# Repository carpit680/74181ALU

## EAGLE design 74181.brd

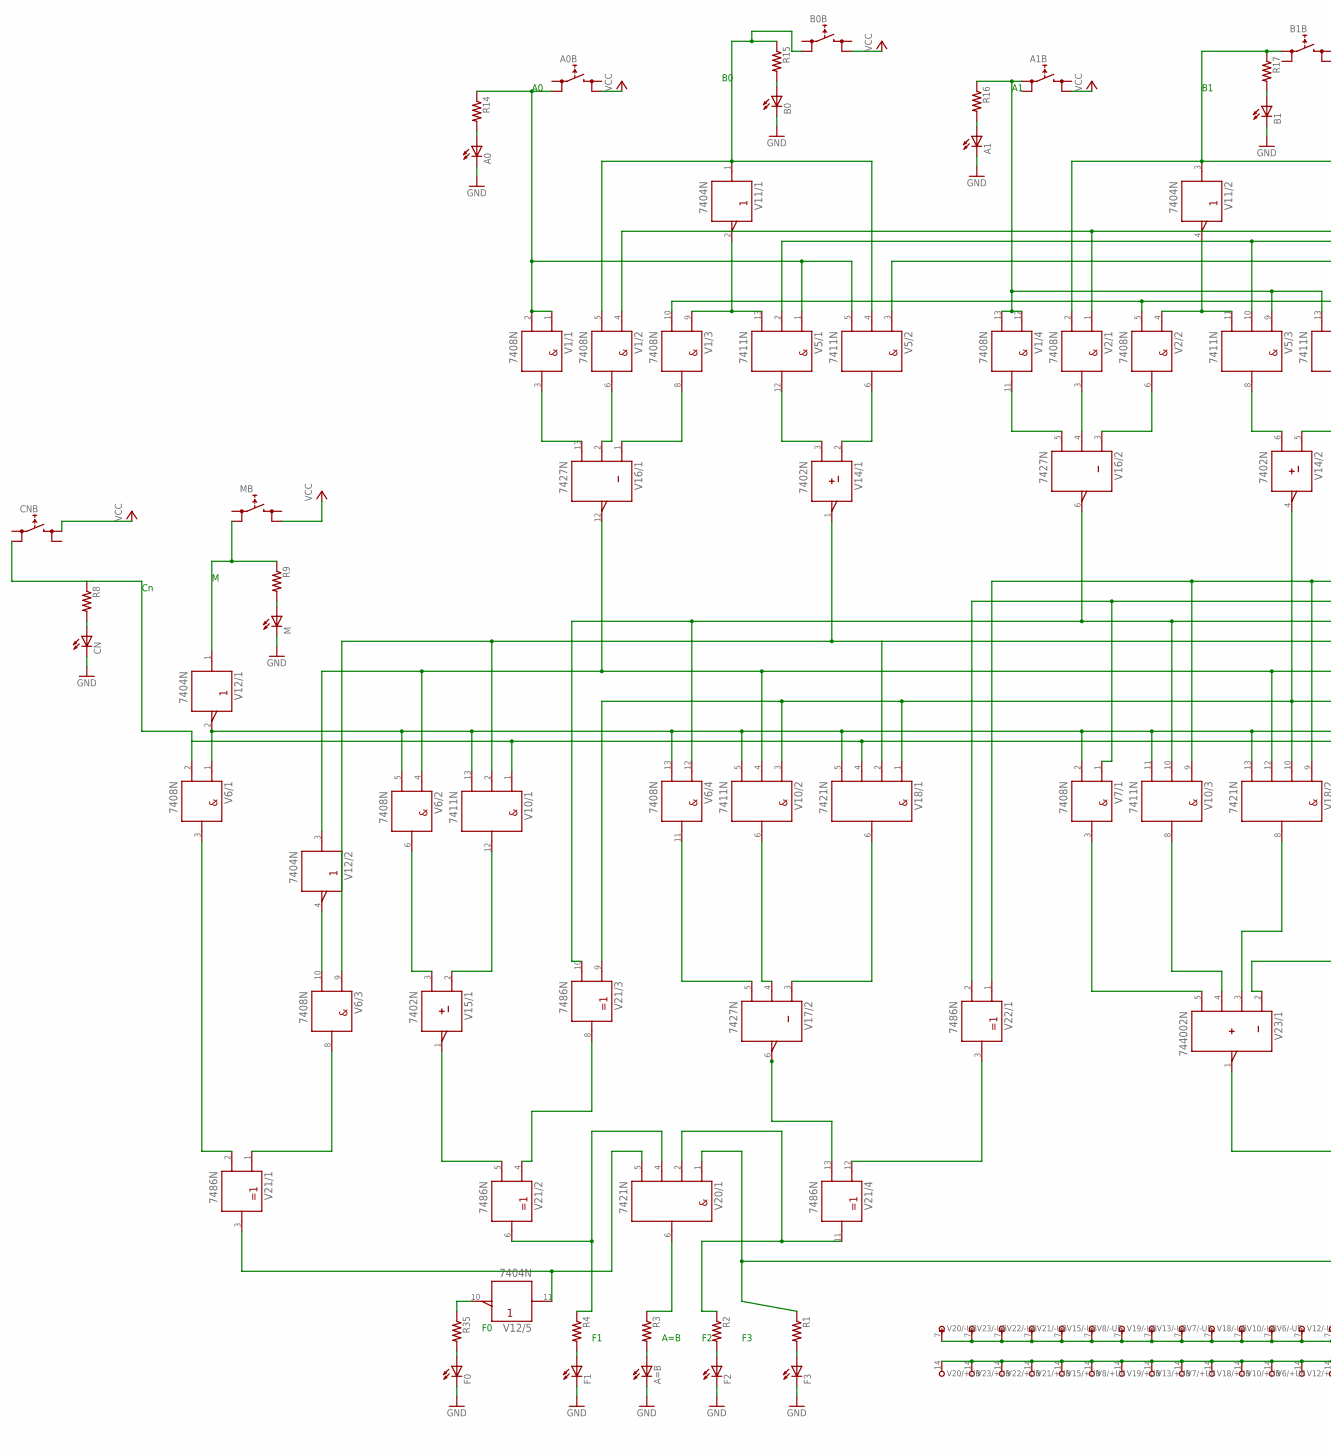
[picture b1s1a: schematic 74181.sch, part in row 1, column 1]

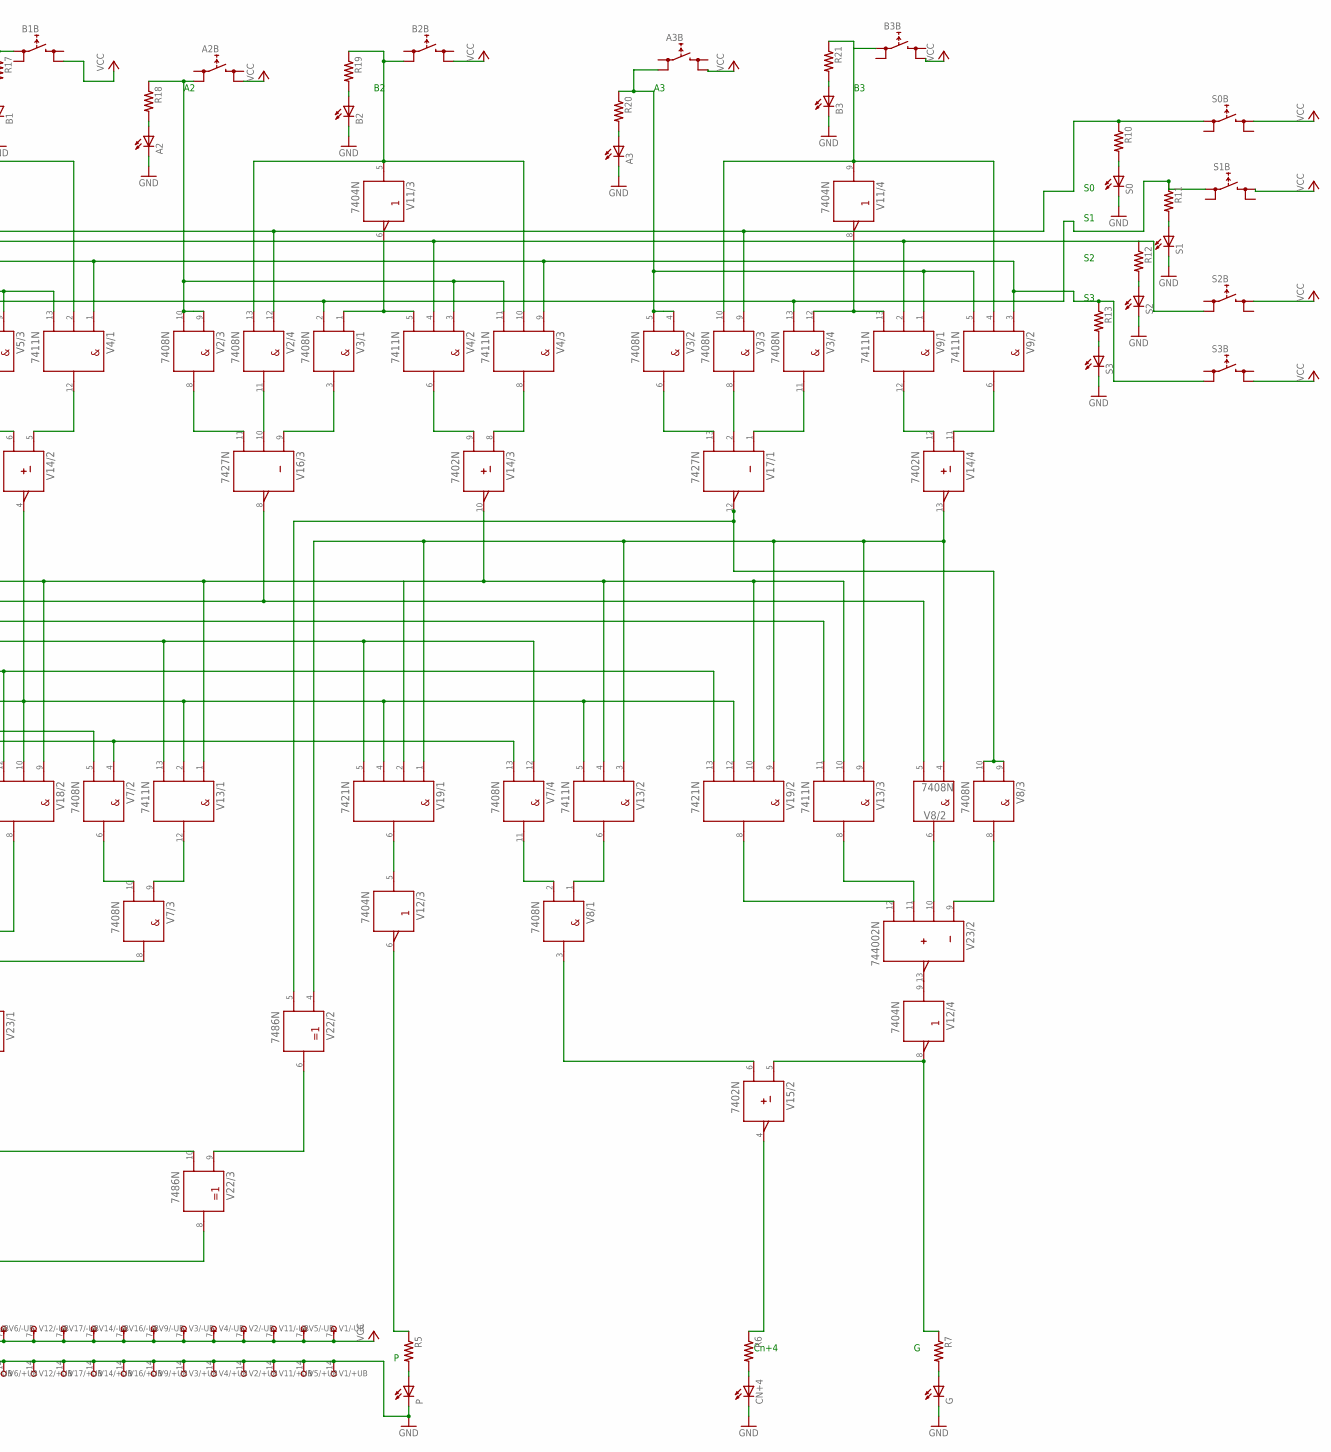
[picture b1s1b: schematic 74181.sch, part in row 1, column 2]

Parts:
A0, A1, A2, A3: LEDCHIP-LED0603; CHIP-LED0603
A0B, A1B, A2B, A3B: REKN
A=B: LEDCHIP-LED0603; CHIP-LED0603
B0, B1, B2, B3: LEDCHIP-LED0603; CHIP-LED0603
B0B, B1B, B2B, B3B: REKN
CN: LEDCHIP-LED0603; CHIP-LED0603
CN+4: LEDCHIP-LED0603; CHIP-LED0603
CNB: REKN
F0, F1, F2, F3: LEDCHIP-LED0603; CHIP-LED0603
G: LEDCHIP-LED0603; CHIP-LED0603
M: LEDCHIP-LED0603; CHIP-LED0603
MB: REKN
P: LEDCHIP-LED0603; CHIP-LED0603
R1, R2, R3, R4, R5, R6, R7, R8, R9, R10, R11, R12, R13, R14, R15, R16, R17, R18, R19, R20, R21, R35: R-US_R0603; R0603
S0, S1, S2, S3: LEDCHIP-LED0603; CHIP-LED0603
S0B, S1B, S2B, S3B: REKN
V1, V2, V3, V6, V7, V8: 7408N; DIL14
V4, V5, V9, V10, V13: 7411N; DIL14
V11, V12: 7404N; DIL14
V14, V15: 7402N; DIL14
V16, V17: 7427N; DIL14
V18, V19, V20: 7421N; DIL14
V21, V22: 7486N; DIL14
V23: 744002N; DIL14

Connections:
!F!0: V12.11 (A), V20.5 (D), V21.3 (Y)
GND: A0.C, A1.C, A2.C, A3.C, A=B.C, B0.C, B1.C, B2.C, B3.C, CN.C, CN+4.C, F0.C, F1.C, F2.C, F3.C, G.C, M.C, P.C, S0.C, S1.C, S2.C, S3.C, V1.14 (+UB), V2.14 (+UB), V3.14 (+UB), V4.14 (+UB), V5.14 (+UB), V6.14 (+UB), V7.14 (+UB), V8.14 (+UB), V9.14 (+UB), V10.14 (+UB), V11.14 (+UB), V12.14 (+UB), V13.14 (+UB), V14.14 (+UB), V15.14 (+UB), V16.14 (+UB), V17.14 (+UB), V18.14 (+UB), V19.14 (+UB), V20.14 (+UB), V21.14 (+UB), V22.14 (+UB), V23.14 (+UB)
unnamed: V1.9 (A), V5.13 (C), V11.2 (Y)
unnamed: V2.4 (A), V5.11 (C), V11.4 (Y)
unnamed: V3.1 (A), V4.5 (C), V11.6 (Y)
unnamed: V3.12 (A), V9.13 (C), V11.8 (Y)
unnamed: V1.3 (Y), V16.13 (C)
unnamed: V1.6 (Y), V16.2 (B)
unnamed: V1.8 (Y), V16.1 (A)
unnamed: V5.12 (Y), V14.3 (B)
unnamed: V5.6 (Y), V14.2 (A)
unnamed: V1.11 (Y), V16.5 (C)
unnamed: V2.3 (Y), V16.4 (B)
unnamed: V2.6 (Y), V16.3 (A)
unnamed: V5.8 (Y), V14.6 (B)
unnamed: V4.12 (Y), V14.5 (A)
unnamed: V2.8 (Y), V16.11 (C)
unnamed: V2.11 (Y), V16.10 (B)
unnamed: V3.3 (Y), V16.9 (A)
unnamed: V4.6 (Y), V14.9 (B)
unnamed: V4.8 (Y), V14.8 (A)
unnamed: V3.6 (Y), V17.13 (C)
unnamed: V3.8 (Y), V17.2 (B)
unnamed: V3.11 (Y), V17.1 (A)
unnamed: V9.12 (Y), V14.12 (B)
unnamed: V9.6 (Y), V14.11 (A)
unnamed: V6.1 (A), V6.5 (B), V6.13 (B), V7.2 (B), V7.5 (B), V10.5 (C), V10.11 (C), V10.13 (C), V12.2 (Y), V18.5 (D), V18.13 (D)
unnamed: V6.10 (B), V12.4 (Y)
unnamed: R4.1, V20.4 (C), V21.6 (Y)
unnamed: F3.A, R1.2
unnamed: R2.1, V20.2 (B), V21.11 (Y)
unnamed: R1.1, V20.1 (A), V22.8 (Y)
unnamed: V7.3 (Y), V23.5 (D)
unnamed: V10.8 (Y), V23.4 (C)
unnamed: V18.8 (Y), V23.3 (B)
unnamed: V7.8 (Y), V23.2 (A)
unnamed: V7.6 (Y), V7.10 (B)
unnamed: V7.9 (A), V13.12 (Y)
unnamed: V22.10 (B), V23.1 (Y)
unnamed: V22.6 (Y), V22.9 (A)
unnamed: V12.5 (A), V19.6 (Y)
unnamed: V8.1 (A), V13.6 (Y)
unnamed: V12.9 (A), V23.13 (Y)
unnamed: R7.1, V12.8 (Y), V15.5 (A)
unnamed: V8.3 (Y), V15.6 (B)
unnamed: V19.8 (Y), V23.12 (D)
unnamed: V13.8 (Y), V23.11 (C)
unnamed: V8.8 (Y), V23.9 (A)
unnamed: V6.3 (Y), V21.2 (B)
unnamed: V6.8 (Y), V21.1 (A)
unnamed: V6.6 (Y), V15.3 (B)
unnamed: V10.12 (Y), V15.2 (A)
unnamed: V15.1 (Y), V21.5 (B)
unnamed: V21.4 (A), V21.8 (Y)
unnamed: V21.12 (A), V22.3 (Y)
unnamed: V6.11 (Y), V17.5 (C)
unnamed: V10.6 (Y), V17.4 (B)
unnamed: V17.3 (A), V18.6 (Y)
unnamed: R5.1, V12.6 (Y)
unnamed: R6.1, V15.4 (Y)
unnamed: R3.1, V20.6 (Y)
unnamed: V6.9 (A), V7.12 (A), V10.2 (B), V13.13 (C), V14.1 (Y), V18.2 (B), V19.5 (D)
unnamed: CNB.0B (0), R8.1, V6.2 (B), V7.4 (A), V7.13 (B), V10.1 (A), V18.4 (C)
unnamed: V6.4 (A), V10.4 (B), V12.3 (A), V16.12 (Y), V18.12 (C), V19.13 (D)
unnamed: V6.12 (A), V10.10 (B), V13.11 (C), V16.6 (Y), V21.10 (B)
unnamed: V8.9 (A), V8.10 (B), V22.5 (B)
unnamed: A0B.0B (0), R14.1, V1.1 (A), V1.2 (B), V5.1 (A), V5.5 (C)
unnamed: A1B.0A (0), R16.1, V1.12 (A), V1.13 (B), V4.13 (C), V5.9 (A)
unnamed: A2B.0B (0), R18.1, V2.10 (B), V4.3 (A), V4.11 (C)
unnamed: A3B.0B (0), R20.1, V3.5 (B), V9.1 (A), V9.5 (C)
unnamed: V10.3 (A), V13.2 (B), V13.5 (C), V14.4 (Y), V18.1 (A), V18.10 (B), V19.4 (C), V19.12 (C), V21.9 (A)
unnamed: V7.1 (A), V8.5 (B), V16.8 (Y), V22.2 (B)
unnamed: V10.9 (A), V13.1 (A), V13.4 (B), V13.10 (B), V14.10 (Y), V18.9 (A), V19.2 (B), V19.10 (B), V22.1 (A)
unnamed: R11.1, S1B.0A (0), V1.10 (B), V2.5 (B), V3.2 (B), V3.13 (B)
unnamed: R10.1, S0B.0A (0), V1.4 (A), V2.1 (A), V2.12 (A), V3.9 (A)
unnamed: V8.4 (A), V13.3 (A), V13.9 (A), V14.13 (Y), V19.1 (A), V19.9 (A), V22.4 (A)
unnamed: MB.0B (0), R9.1, V12.1 (A)
unnamed: B0B.0B (0), R15.1, V1.5 (B), V5.4 (B), V11.1 (A)
unnamed: B1B.0A (0), R17.1, V2.2 (B), V4.2 (B), V11.3 (A)
unnamed: B2B.0B (0), R19.1, V2.13 (B), V4.10 (B), V11.5 (A)
unnamed: B3B.0A (0), R21.1, V3.10 (B), V9.4 (B), V11.9 (A)
unnamed: R13.1, S3B.0B (0), V4.1 (A), V4.9 (A), V5.3 (A), V9.3 (A)
unnamed: R12.1, S2B.0B (0), V4.4 (B), V5.2 (B), V5.10 (B), V9.2 (B)
unnamed: V7.11 (Y), V8.2 (B)
unnamed: V8.6 (Y), V23.10 (B)
unnamed: V17.6 (Y), V17.12 (Y)
unnamed: F2.A, R2.2
unnamed: A=B.A, R3.2
unnamed: F1.A, R4.2
unnamed: P.A, R5.2
unnamed: F0.A, R35.2
unnamed: CN+4.A, R6.2
unnamed: G.A, R7.2
unnamed: CN.A, R8.2
unnamed: M.A, R9.2
unnamed: R10.2, S0.A
unnamed: R11.2, S1.A
unnamed: R12.2, S2.A
unnamed: R13.2, S3.A
unnamed: A0.A, R14.2
unnamed: B0.A, R15.2
unnamed: A1.A, R16.2
unnamed: B1.A, R17.2
unnamed: A2.A, R18.2
unnamed: B2.A, R19.2
unnamed: A3.A, R20.2
unnamed: B3.A, R21.2
unnamed: R35.1, V12.10 (Y)
VCC: A0B.1B (1), A1B.1B (1), A2B.1B (1), A3B.1B (1), B0B.1B (1), B1B.1B (1), B2B.1B (1), B3B.1B (1), CNB.1A (1), MB.1B (1), S0B.1A (1), S1B.1A (1), S2B.1A (1), S3B.1B (1), V1.7 (-UB), V2.7 (-UB), V3.7 (-UB), V4.7 (-UB), V5.7 (-UB), V6.7 (-UB), V7.7 (-UB), V8.7 (-UB), V9.7 (-UB), V10.7 (-UB), V11.7 (-UB), V12.7 (-UB), V13.7 (-UB), V14.7 (-UB), V15.7 (-UB), V16.7 (-UB), V17.7 (-UB), V18.7 (-UB), V19.7 (-UB), V20.7 (-UB), V21.7 (-UB), V22.7 (-UB), V23.7 (-UB)

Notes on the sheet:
A=B
Cn+4

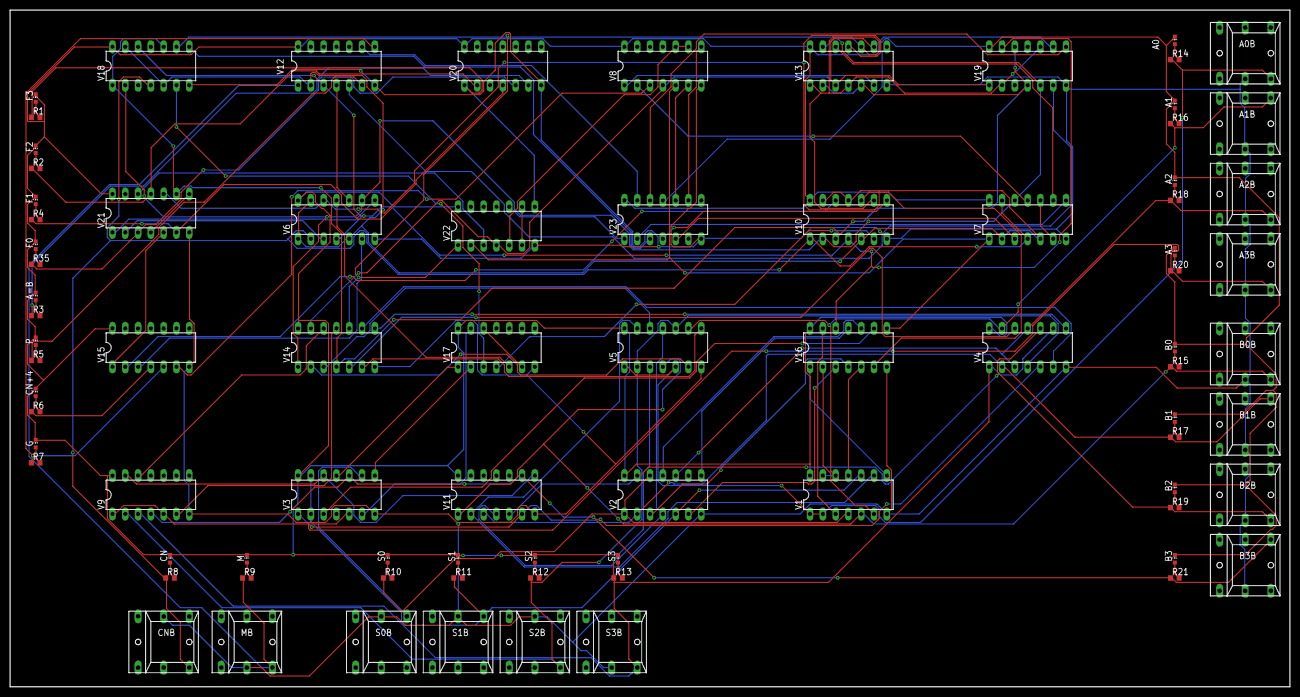
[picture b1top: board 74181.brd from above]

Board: 4 copper layers, 254.0 x 134.3 mm, 81 parts (0 on the bottom side), 109 nets.

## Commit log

2019-12-03 Added a missing not gate to F0 output.
